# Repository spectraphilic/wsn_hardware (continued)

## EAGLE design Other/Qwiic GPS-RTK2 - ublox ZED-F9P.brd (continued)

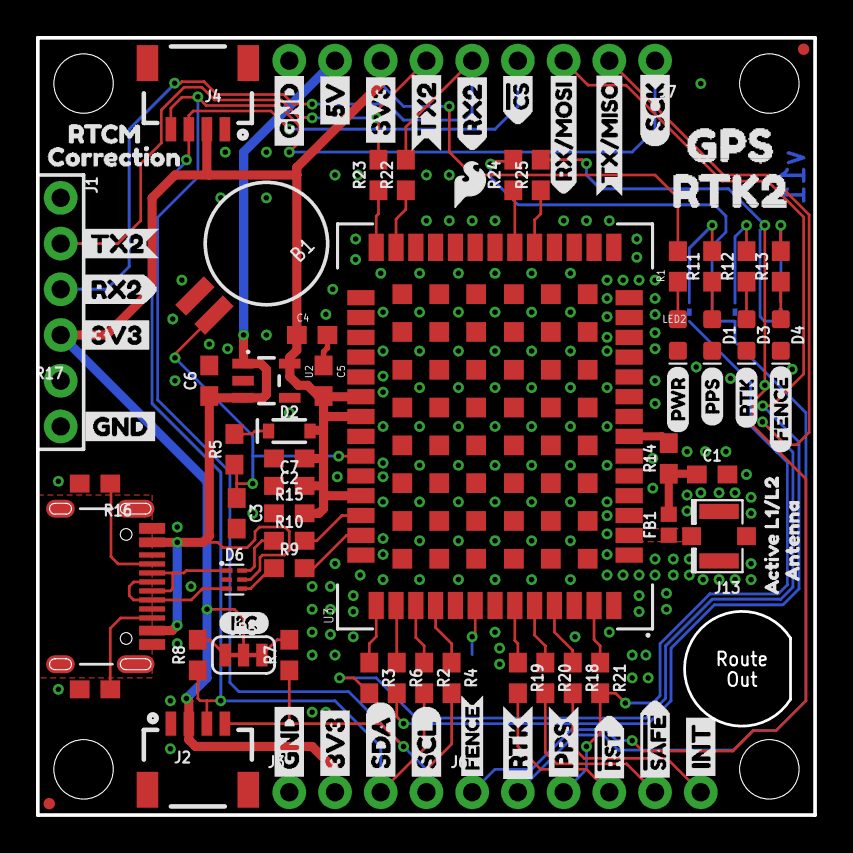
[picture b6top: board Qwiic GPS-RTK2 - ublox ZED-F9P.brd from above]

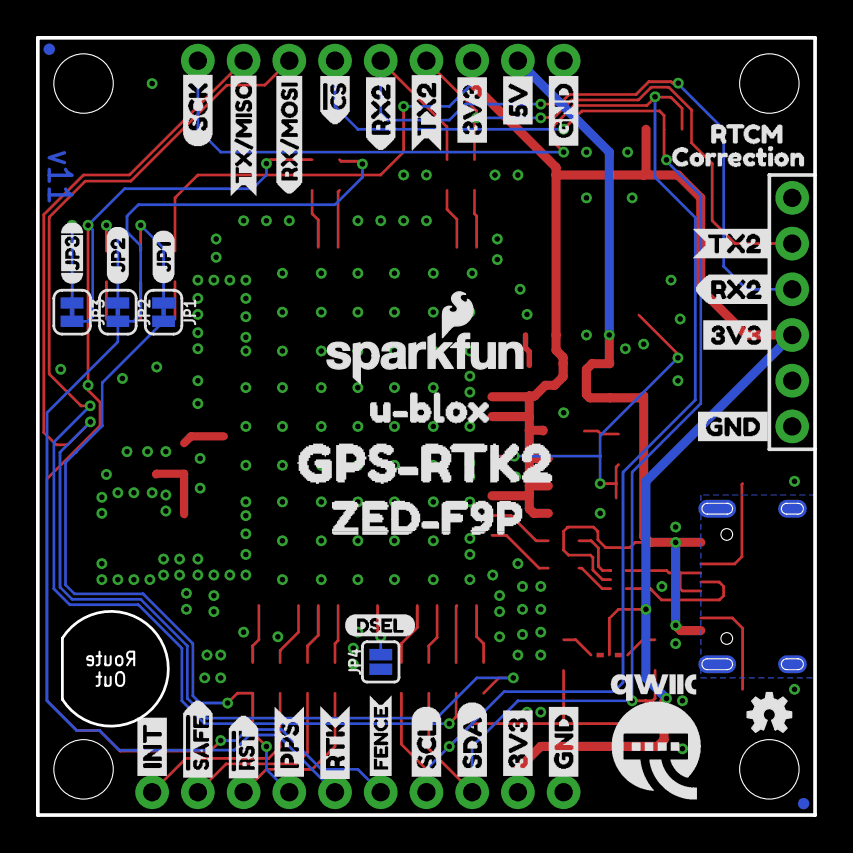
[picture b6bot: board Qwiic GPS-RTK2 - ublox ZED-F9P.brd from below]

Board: 2 copper layers, 43.2 x 43.2 mm, 136 parts (41 on the bottom side), 51 nets.

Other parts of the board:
U$1, U$4: SDA-[)
U$3, U$5: SCL-[)
U$6, U$7, U$60, U$61, U$66, U$67: 3V3-04
U$8, U$9, U$62, U$63: GND-04
U$10: I_SUPER2_C-()-03
U$11: FENCE2
U$12: JP20
U$13, U$28, U$29: RTK1
U$14, U$17: FENCE0
U$15, U$16: INT8
U$18: PWR-()-03
U$19, U$20: 5V
U$21, U$56, U$58: RX20
U$22: U#BLOX3
U$23, U$24: CS#-<]
U$25: JP10
U$26, U$31: RX#MOSI3
U$27: DSEL0
U$30: QWIIC-LOGO-MEDIUM
U$32: JP32
U$33: SFE_LOGO_FLAME_.1
U$34, U$37: TX#MISO1
U$35, U$36: #RST3
U$38, U$41: SCK-(]-04
U$39, U$40: #SAFE1
U$42: RX22
U$43, U$44: PPS5
U$45, U$68: GND3
U$46: GPS#RTK28
U$48, U$70: RTCM5
U$49: ZED#F9P6
U$50, U$55, U$57: TX21
U$51: TX23
U$52: PPS0
U$53, U$69: CORRECTION0
U$59: GPS0
U$64: RTK21
U$65: ACTIVE_L1#L21
U$71: ANTENNA2

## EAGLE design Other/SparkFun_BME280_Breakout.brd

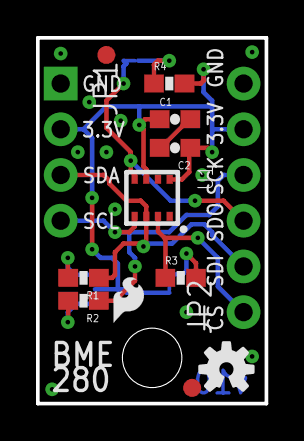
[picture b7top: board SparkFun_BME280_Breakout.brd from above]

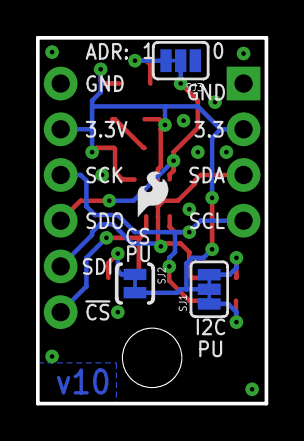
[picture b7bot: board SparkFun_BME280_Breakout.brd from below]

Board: 2 copper layers, 12.7 x 20.3 mm, 19 parts (4 on the bottom side), 10 nets.

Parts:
C1, C2: 0.1uF; 0603-CAP
FID1, FID2: FIDUCIAL1X2; FIDUCIAL-1X2
FRAME1: FRAME-LETTER; CREATIVE_COMMONS
JP1: 1X04_NO_SILK
JP2: 1X06_NO_SILK
LOGO1, LOGO2: SFE_LOGO_FLAME.1_INCH; SFE_LOGO_FLAME_.1
LOGO3: OSHW-LOGOS; OSHW-LOGO-S
R1, R2, R3, R4: 4.7K; 0603-RES
SJ1: EN I2C PULL; PAD-JUMPER-3-3OF3_NC_BY_TRACE_YES_SILK_FULL_BOX
SJ2: EN I2C MODE; PAD-JUMPER-2-NC_BY_TRACE_YES_SILK
SJ3: EN ADR PULLUP; PAD-JUMPER-3-2OF3_NC_BY_TRACE_YES_SILK_FULL_BOX
STANDOFF4: STAND-OFF
U1: BME280; BME280_LGA

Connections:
3.3V: C1.1, C2.1, JP1.2, JP2.5, R4.2, SJ1.2, SJ2.2, U1.P$6, U1.P$8
!CS: JP2.1, R3.1, U1.P$2
GND: C1.2, C2.2, JP1.1, JP2.6, SJ3.1, U1.P$1, U1.P$7
unnamed: R1.2, SJ1.3
unnamed: R2.2, SJ1.1
unnamed: R3.2, SJ2.1
unnamed: R4.1, SJ3.3
SCK/SCL: JP1.4, JP2.4, R2.1, U1.P$4
SDI/SDA: JP1.3, JP2.2, R1.1, U1.P$3
SDO/ADR: JP2.3, SJ3.2, U1.P$5
